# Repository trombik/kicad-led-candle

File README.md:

# LED candle

A simple LED candle using ATTiny AVR MCUs.

## Building

```console
pio run
```

or building a specific target

```console
pio run -e attiny13a
```

## Build flags

### White noise

`-D USING_WHITE_NOISE` uses `rand()`, instead of "pink" noise, for changing
the duty. Requires more flash memory.

### Floating point math

`-D USING_PINK_NOISE_FLOAT` uses floating point math version of `pink_noise()`.
Requires more flash memory.

## Debugging

```console
pio debug -e attiny13a --interface=gdb -- -x init
```

# LICENSE

MIT. See [LICENSE](LICENSE).

[tiny_random.c](src/tiny_random.c) and [tiny_random.h](src/tiny_random.h) are
licensed under 3-clause BSD license.

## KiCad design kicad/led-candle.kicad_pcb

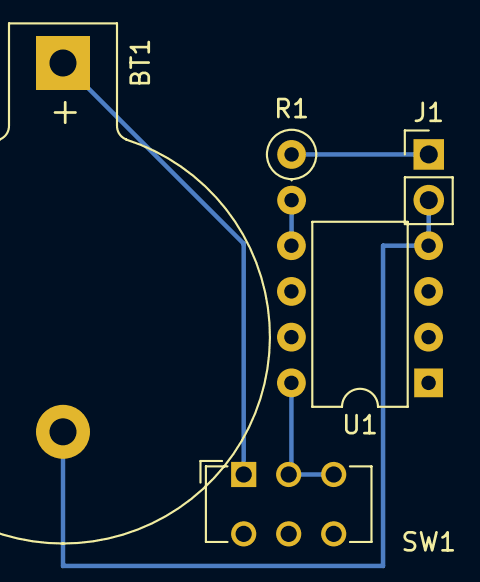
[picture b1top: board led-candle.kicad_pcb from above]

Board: 2 copper layers, 5 parts (0 on the bottom side), 5 nets.

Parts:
BT1: Battery_Cell; BatteryHolder_Keystone_103_1x20mm
J1: Conn_01x02; PinHeader_1x02_P2.54mm_Vertical
R1: 220; R_Axial_DIN0207_L6.3mm_D2.5mm_P2.54mm_Vertical
SW1: SW_SPDT; SW_CuK_JS202011CQN_DPDT_Straight
U1: ATtiny13A-P; DIP-8_W7.62mm

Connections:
GND: BT1.2 (-), J1.2, U1.4 (GND)
LED: J1.1, R1.1
unnamed: BT1.1 (+), SW1.1 (A)
unnamed: R1.2, U1.5 (PB0)
VCC: SW1.2 (B), SW1.3 (C), U1.8 (VCC)

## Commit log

2022-08-17 feat: initial implementation
2022-08-17 feat: add the 3D models
2022-08-17 doc: add schematic
2022-08-17 doc: add README
2022-08-17 doc: add LICENSE
2022-08-17 doc: document debugging on simavr
2022-08-18 feat: add PCB layout, remove optional LED from schematic
2022-08-18 feat: add project file for "fire"
2022-08-18 doc: add schmatic SVG file
2022-08-18 bugfix: fix a track in PCB
2022-08-18 bugfix: fix a link in README
2022-08-18 doc: add flipped PCB board in PDF
2022-08-29 bugfix: format, and use pinMode() instead of resister access
2022-08-29 doc: add some pics
2022-08-29 chore: add clang-format
2022-08-29 bugfix: fix URLs to images
2022-08-29 doc: add 3d model image
2022-08-29 doc: add a movie in gif
2022-09-06 ci: add GitHub Actions build workflow
